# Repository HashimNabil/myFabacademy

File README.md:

# myFabacademy
This repo contains all my fabacademy 2017 source files / goo.gl/bh3s8U

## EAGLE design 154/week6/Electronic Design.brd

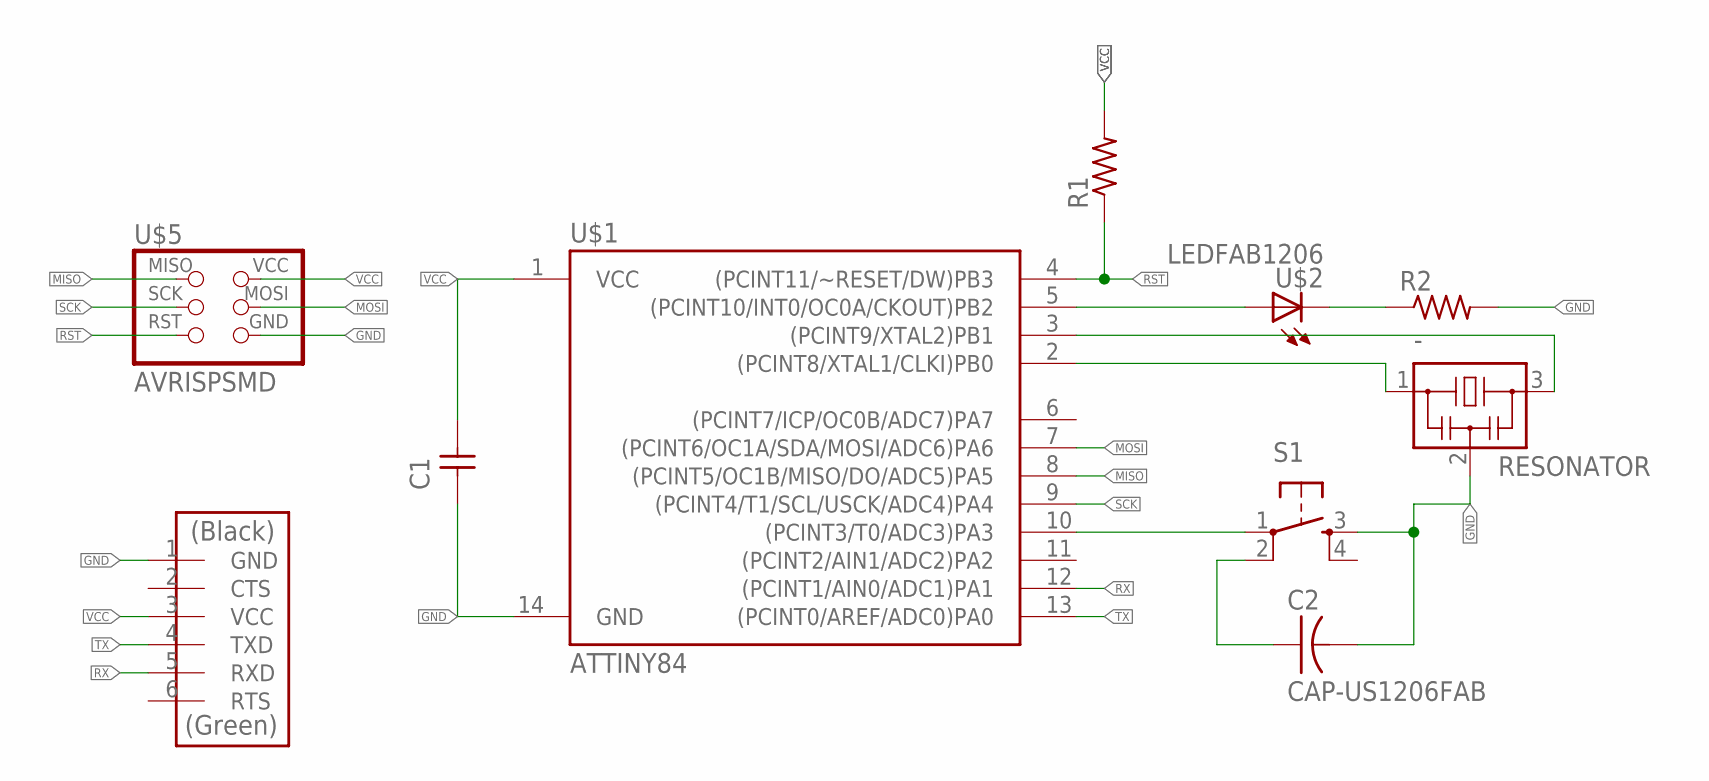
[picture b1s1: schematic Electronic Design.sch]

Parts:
-: RESONATOR; EFOBM
C1: CAP-UNPOLARIZEDFAB; C1206FAB
C2: CAP-US1206FAB; C1206FAB
R1, R2: RES-US1206FAB; R1206FAB
S1: 6MM_SWITCH6MM_SWITCH; 6MM_SWITCH
U$1: ATTINY84; SO14
U$2: LEDFAB1206; LED1206FAB
U$3: FTDI-SMD-HEADER; 1X06SMD
U$5: AVRISPSMD; 2X03SMD

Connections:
BUTTON: C2.1, S1.2 (P1)
GND: -.2, C1.1, C2.2, R2.2, S1.3 (S), U$1.14 (GND), U$3.1 (GND), U$5.6 (GND)
MISO: U$1.8 ((PCINT5/OC1B/MISO/DO/ADC5)PA5), U$5.1 (MISO)
MOSI: U$1.7 ((PCINT6/OC1A/SDA/MOSI/ADC6)PA6), U$5.4 (MOSI)
unnamed: R2.1, U$2.2 (C)
unnamed: U$1.5 ((PCINT10/INT0/OC0A/CKOUT)PB2), U$2.1 (A)
unnamed: S1.1, U$1.10 ((PCINT3/T0/ADC3)PA3)
RST: R1.1, U$1.4 ((PCINT11/~RESET/DW)PB3), U$5.5 (RST)
RX: U$1.12 ((PCINT1/AIN0/ADC1)PA1), U$3.5 (RXD)
SCK: U$1.9 ((PCINT4/T1/SCL/USCK/ADC4)PA4), U$5.3 (SCK)
TX: U$1.13 ((PCINT0/AREF/ADC0)PA0), U$3.4 (TXD)
VCC: C1.2, R1.2, U$1.1 (VCC), U$3.3 (VCC), U$5.2 (VCC)
XTAL1: -.1, U$1.2 ((PCINT8/XTAL1/CLKI)PB0)
XTAL2: -.3, U$1.3 ((PCINT9/XTAL2)PB1)

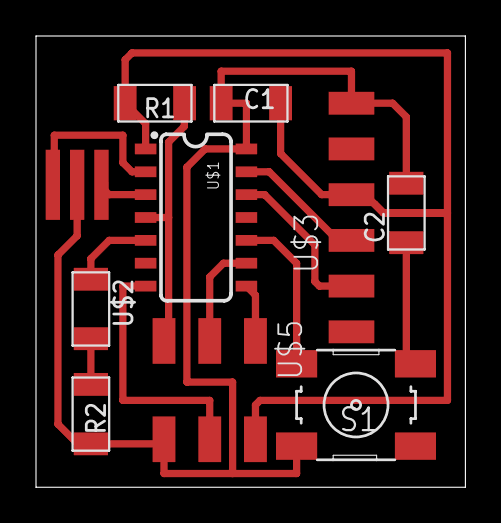
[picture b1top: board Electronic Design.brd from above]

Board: 2 copper layers, 23.9 x 25.1 mm, 10 parts (0 on the bottom side), 14 nets.

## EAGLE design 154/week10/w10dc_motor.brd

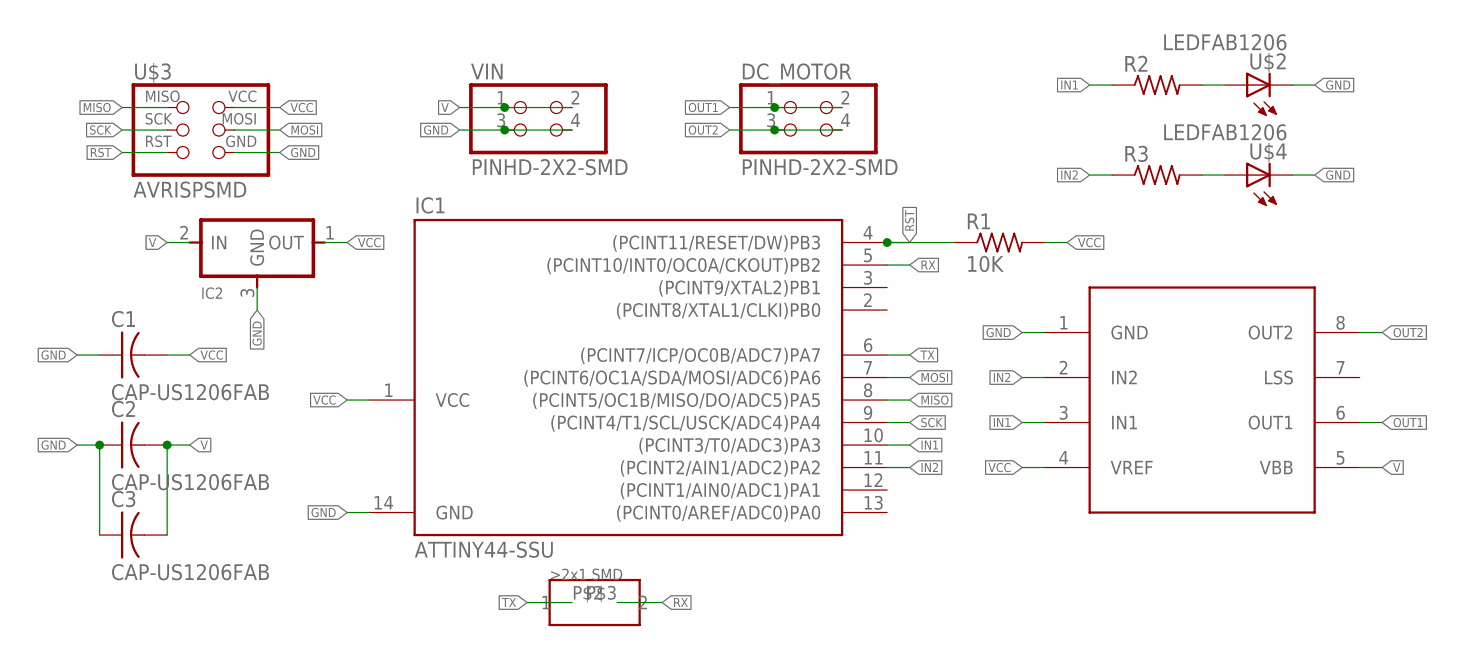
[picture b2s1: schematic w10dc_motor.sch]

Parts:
C1, C2, C3: CAP-US1206FAB; C1206FAB
DC_MOTOR: PINHD-2X2-SMD; 2X02SMD
IC1: ATTINY44-SSU; SOIC14
IC2: REGULATORSOT23; SOT23
R1: 10K; R1206FAB
R2, R3: RES-US1206FAB; R1206FAB
U$1: A4953-H-BRIDGE-MOTOR-DRIVER; SOIC8
U$2, U$4: LEDFAB1206; LED1206FAB
U$3: AVRISPSMD; 2X03SMD
U$5: 2X1SMD; PINHD-2X1-SMD
VIN: PINHD-2X2-SMD; 2X02SMD

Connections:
GND: C1.1, C2.1, C3.1, IC1.14 (GND), IC2.3 (GND), U$1.1 (GND), U$2.2 (C), U$3.6 (GND), U$4.2 (C), VIN.3, VIN.4
IN1: IC1.10 ((PCINT3/T0/ADC3)PA3), R2.1, U$1.3 (IN1)
IN2: IC1.11 ((PCINT2/AIN1/ADC2)PA2), R3.1, U$1.2 (IN2)
MISO: IC1.8 ((PCINT5/OC1B/MISO/DO/ADC5)PA5), U$3.1 (MISO)
MOSI: IC1.7 ((PCINT6/OC1A/SDA/MOSI/ADC6)PA6), U$3.4 (MOSI)
unnamed: R2.2, U$2.1 (A)
unnamed: R3.2, U$4.1 (A)
OUT1: DC_MOTOR.1, DC_MOTOR.2, U$1.6 (OUT1)
OUT2: DC_MOTOR.3, DC_MOTOR.4, U$1.8 (OUT2)
RST: IC1.4 ((PCINT11/RESET/DW)PB3), R1.1, U$3.5 (RST)
RX: IC1.5 ((PCINT10/INT0/OC0A/CKOUT)PB2), U$5.P$3 (2)
SCK: IC1.9 ((PCINT4/T1/SCL/USCK/ADC4)PA4), U$3.3 (SCK)
TX: IC1.6 ((PCINT7/ICP/OC0B/ADC7)PA7), U$5.P$2 (1)
V: C2.2, C3.2, IC2.2 (IN), U$1.5 (VBB), VIN.1, VIN.2
VCC: C1.2, IC1.1 (VCC), IC2.1 (OUT), R1.2, U$1.4 (VREF), U$3.2 (VCC)

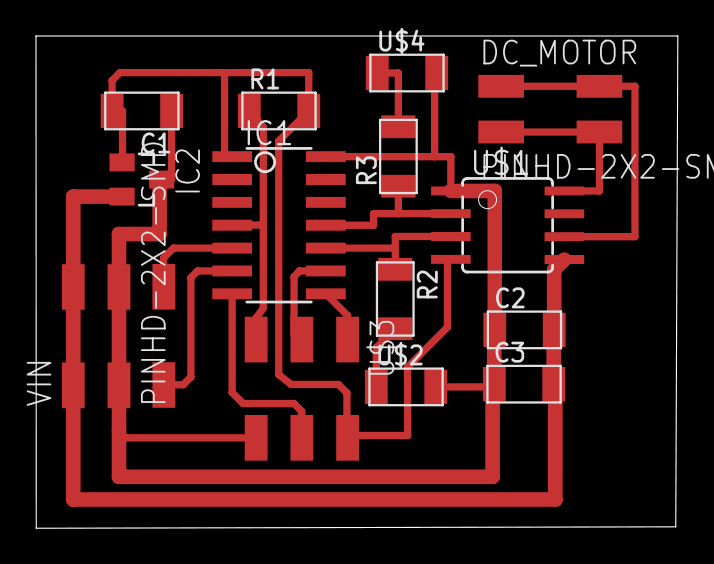
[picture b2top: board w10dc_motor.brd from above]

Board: 2 copper layers, 35.7 x 27.3 mm, 15 parts (0 on the bottom side), 15 nets.

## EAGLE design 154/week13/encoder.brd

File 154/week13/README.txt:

Image Slider Maker README
=========================
ImageSliderMaker.com

Using in your website
---------------------

Please first make sure you have fully extracted the contents of the zip file.
In Windows, right-click on imageslidermaker.zip and select Extract All...

To get your slider working in your web page, you must add
my-slider.css, ism-2.2.min.js and the slide images to your project
directory and paste the markup (included below) into your HTML.

The directory structure of this package:

  imageslidermaker/
    README.txt
    example.html
    ism/
      css/
        my-slider.css
      js/
        ism-2.2.min.js
      image/
        slides/
          flower-729514_1280.jpg
          beautiful-701678_1280.jpg
          summer-192179_1280.jpg

For a working example, open example.html in your web browser or
follow the instructions below to integrate the slider into your
project.

Step by step instructions
-------------------------

1. Paste the following into the head of your HTML file:

<link rel="stylesheet" href="ism/css/my-slider.css"/>
<script src="ism/js/ism-2.2.min.js"></script>

2. Paste this into the body of your HTML file (at the location where:
   you would like your slider to appear in the page):

<div class="ism-slider" id="my-slider">
  <ol>
    <li>
      
      <div class="ism-caption ism-caption-0">My slide caption text</div>
    </li>
    <li>
      
      <div class="ism-caption ism-caption-0">My slide caption text</div>
    </li>
    <li>
      
      <div class="ism-caption ism-caption-0">My slide caption text</div>
    </li>
  </ol>
</div>
<p class="ism-badge" id="my-slider-ism-badge"><a class="ism-link" href="http://imageslidermaker.com" rel="nofollow">generated with ISM</a></p>

3. Copy the ism/ directory into the root directory of your project.

   The css, js and image paths are relative, meaning the ism/
   directory should be in the same directory (path) as your HTML
   file containing the slider.

Support
-------

If you need support or have a suggestion please get in touch using
the contact form at ImageSliderMaker.com/contact or send an email
to support@imageslidermaker.com

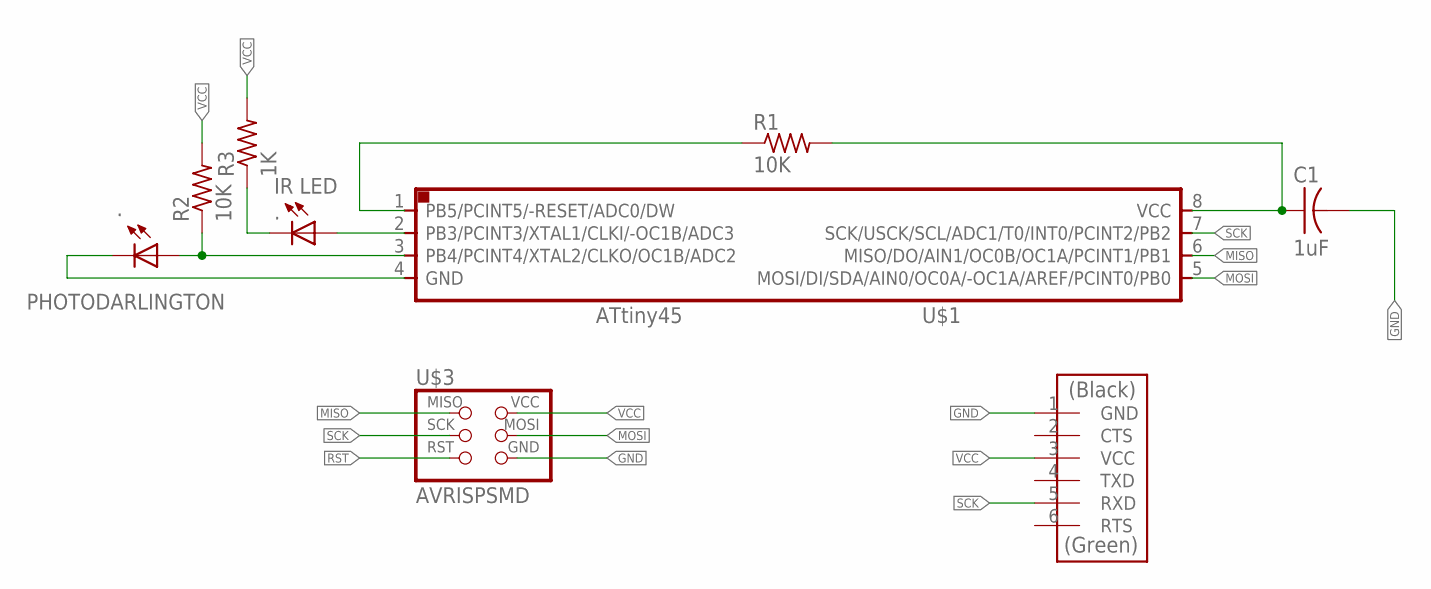
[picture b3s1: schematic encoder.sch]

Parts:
.: IR LED; LED1206FAB
C1: 1uF; C1206FAB
FTDI: FTDI-SMD-HEADER; 1X06SMD
PHOTODARLINGTON: .; LED1206
R1, R2: 10K; R1206FAB
R3: 1K; R1206FAB
U$1: ATTINY45SI; SOIC8
U$3: AVRISPSMD; 2X03SMD

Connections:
GND: C1.2, FTDI.1 (GND), PHOTODARLINGTON.2 (C), U$1.4 (GND), U$3.6 (GND)
MISO: U$1.6 (MISO/DO/AIN1/OC0B/OC1A/PCINT1/PB1), U$3.1 (MISO)
MOSI: U$1.5 (MOSI/DI/SDA/AIN0/OC0A/-OC1A/AREF/PCINT0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), U$3.4 (MOSI)
unnamed: ..1 (A), U$1.2 (PB3/PCINT3/XTAL1/CLKI/-OC1B/ADC3)
unnamed: ..2 (C), R3.1
R2: PHOTODARLINGTON.1 (A), R2.1, U$1.3 (PB4/PCINT4/XTAL2/CLKO/OC1B/ADC2)
RST: R1.1, U$1.1 (PB5/PCINT5/-RESET/ADC0/DW), U$3.5 (RST)
SCK: FTDI.5 (RXD), U$1.7 (SCK/USCK/SCL/ADC1/T0/INT0/PCINT2/PB2), U$3.3 (SCK)
VCC: C1.1, FTDI.3 (VCC), R1.2, R2.2, R3.2, U$1.8 (VCC), U$3.2 (VCC)

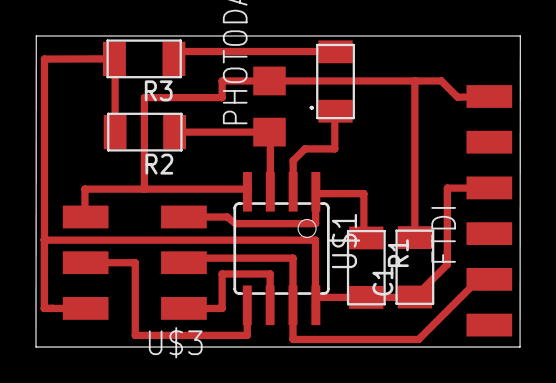
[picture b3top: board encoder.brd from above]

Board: 2 copper layers, 26.9 x 17.3 mm, 9 parts (0 on the bottom side), 9 nets.

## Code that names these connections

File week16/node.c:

//
//
// hello.bus.45.c
//
// 9600 baud serial bus hello-world
//
// Neil Gershenfeld
// 11/24/10
//
// (c) Massachusetts Institute of Technology 2010
// Permission granted for experimental and personal use;
// license for commercial sale available from MIT.
//

#include <avr/io.h>
#include <util/delay.h>
#include <avr/pgmspace.h>
#include <string.h>

#define output(directions,pin) (directions |= pin) // set port direction for output
#define input(directions,pin) (directions &= (~pin)) // set port direction for input
#define set(port,pin) (port |= pin) // set port pin
#define clear(port,pin) (port &= (~pin)) // clear port pin
#define pin_test(pins,pin) (pins & pin) // test for port pin
#define bit_test(byte,bit) (byte & (1 << bit)) // test for bit set
#define bit_delay_time 100 // bit delay for 9600 with overhead
#define bit_delay() _delay_us(bit_delay_time) // RS232 bit delay
#define half_bit_delay() _delay_us(bit_delay_time/2) // RS232 half bit delay
#define led_delay() _delay_ms(1000) // LED flash delay


#define serial_port PORTA
#define serial_direction DDRA
#define serial_pins PINA
#define serial_pin_in (1 << PA0)
#define serial_pin_out (1 << PA1)

#define node_id 'N'

void get_char(volatile unsigned char *pins, unsigned char pin, char *rxbyte) {
   //
   // read character into rxbyte on pins pin
   //    assumes line driver (inverts bits)
   //
   *rxbyte = 0;
   while (pin_test(*pins,pin))
      //
      // wait for start bit
      //
      ;
   //
   // delay to middle of first data bit
   //
   half_bit_delay();
   bit_delay();
   //
   // unrolled loop to read data bits
   //
   if pin_test(*pins,pin)
      *rxbyte |= (1 << 0);
   else
      *rxbyte |= (0 << 0);
   bit_delay();
   if pin_test(*pins,pin)
      *rxbyte |= (1 << 1);
   else
      *rxbyte |= (0 << 1);
   bit_delay();
   if pin_test(*pins,pin)
      *rxbyte |= (1 << 2);
   else
      *rxbyte |= (0 << 2);
   bit_delay();
   if pin_test(*pins,pin)
      *rxbyte |= (1 << 3);
   else
      *rxbyte |= (0 << 3);
   bit_delay();
   if pin_test(*pins,pin)
      *rxbyte |= (1 << 4);
   else
      *rxbyte |= (0 << 4);
   bit_delay();
   if pin_test(*pins,pin)
      *rxbyte |= (1 << 5);
   else
      *rxbyte |= (0 << 5);
   bit_delay();
   if pin_test(*pins,pin)
      *rxbyte |= (1 << 6);
   else
      *rxbyte |= (0 << 6);
   bit_delay();
   if pin_test(*pins,pin)
      *rxbyte |= (1 << 7);
   else
      *rxbyte |= (0 << 7);
   //
   // wait for stop bit
   //
   bit_delay();
   half_bit_delay();
   }

void put_char(volatile unsigned char *port, unsigned char pin, char txchar) {
   //
   // send character in txchar on port pin
   //    assumes line driver (inverts bits)
   //
   // start bit
   //
   clear(*port,pin);
   bit_delay();
   //
   // unrolled loop to write data bits
   //
   if bit_test(txchar,0)
      set(*port,pin);
   else
      clear(*port,pin);
   bit_delay();
   if bit_test(txchar,1)
      set(*port,pin);
   else
      clear(*port,pin);
   bit_delay();
   if bit_test(txchar,2)
      set(*port,pin);
   else
      clear(*port,pin);
   bit_delay();
   if bit_test(txchar,3)
      set(*port,pin);
   else
      clear(*port,pin);
   bit_delay();
   if bit_test(txchar,4)
      set(*port,pin);
   else
      clear(*port,pin);
   bit_delay();
   if bit_test(txchar,5)
      set(*port,pin);
   else
      clear(*port,pin);
   bit_delay();
   if bit_test(txchar,6)
      set(*port,pin);
   else
      clear(*port,pin);
   bit_delay();
   if bit_test(txchar,7)
      set(*port,pin);
   else
      clear(*port,pin);
   bit_delay();
   //
   // stop bit
   //
   set(*port,pin);
   bit_delay();
   //
   // char delay
   //
   bit_delay();
   }

void put_string(volatile unsigned char *port, unsigned char pin, PGM_P str) {
   //
   // send character in txchar on port pin
   //    assumes line driver (inverts bits)
   // function that send stinges letter by letter
   static char chr;
   static int index;
   index = 0;
   do {
      chr = pgm_read_byte(&(str[index]));
      put_char(&serial_port, serial_pin_out, chr);
      ++index;
      } while (chr != 0);
   }
int main(void) {
   //
   // main
   //
  DDRA &= ~(1 << PA3);
  // set PA3 as input in DDRA

  PORTA |= (1 << PA3);
  // SET PULL UP RESISTOR IN PA3
  DDRB |= (1 << PB2);

  // set PB2 as output in DDRB
   static char chr;
   //
   // set clock divider to /1
   //
   CLKPR = (1 << CLKPCE);
   CLKPR = (0 << CLKPS3) | (0 << CLKPS2) | (0 << CLKPS1) | (0 << CLKPS0);
   //
   // initialize output pins
   //
   set(serial_port, serial_pin_out);
   input(serial_direction, serial_pin_out);

      		//PORTB &= ~(1 << PB2);
                PORTB |= ( 1<< PB2);
                led_delay();
      		//PORTB |= ( 1<< PB2);
      		PORTB &= ~(1 << PB2);
                led_delay();

   
   //
   // main loop
   //
   while (1) {
      //get_char(&serial_pins, serial_pin_in, &chr);// this is the command that check for serial messages (like serialRead() in arduino
     get_char(&serial_pins, serial_pin_in, &chr);

      if (chr == 'a') {  // -
      		PORTB &= ~(1 << PB2);
                   }
      else if (chr == 'b') {  // -
      		PORTB |= ( 1<< PB2);
                   }
              }
              }

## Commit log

2018-04-11 added my fabacademy archive
2018-10-21 trying git website hosting service

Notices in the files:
parts and their libraries:
SparkFun-DigitalIC: Licensing: Creative Commons ShareAlike 4.0 International - https://creativecommons.org/licenses/by-sa/4.0
